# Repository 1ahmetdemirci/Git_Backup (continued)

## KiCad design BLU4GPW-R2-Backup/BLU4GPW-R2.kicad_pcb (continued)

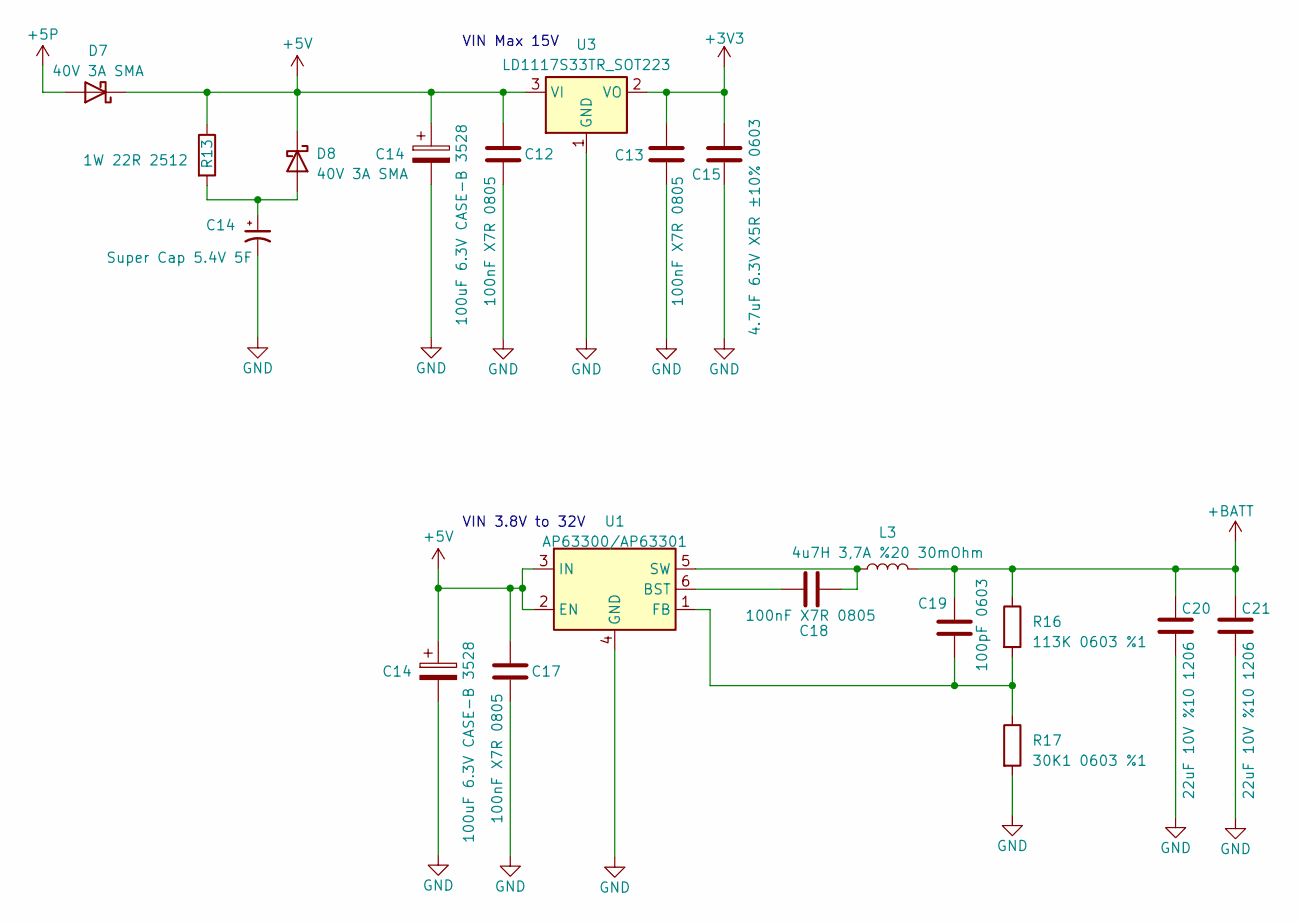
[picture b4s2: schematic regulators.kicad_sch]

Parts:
C12, C13, C17, C18: 100nF X7R 0805; C_0805_2012Metric
C14: Super Cap 5.4V 5F; DRML5R4505
C15: 4.7uF 6.3V X5R ±10% 0603; C_0603_1608Metric
C19: 100pF 0603; C_0603_1608Metric
C20, C21: 22uF 10V %10 1206; C_1206_3216Metric
D7, D8: 40V 3A SMA; D_SMA
L3: 4u7H 3,7A %20 30mOhm; SDR0805-1R5ML
R13: 1W 22R 2512; R_2512_6332Metric
R16: 113K 0603 %1; R_0603_1608Metric
R17: 30K1 0603 %1; R_0603_1608Metric
U1: AP63300/AP63301; AP63300
U3: LD1117S33TR_SOT223; SOT-223-3_TabPin2

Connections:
+5P: D7.2 (A); also elsewhere on the board
+BATT: C19.1, C20.1, C21.1, L3.2, R16.1; also elsewhere on the board
GND: C12.2, C13.2, C14.2, C15.2, C17.2, C20.2, C21.2, R17.2, U1.4 (GND), U3.1 (GND); also elsewhere on the board
unnamed: C18.2, U1.6 (BST)
unnamed: C19.2, R16.2, R17.1, U1.1 (FB)
unnamed: C18.1, L3.1, U1.5 (SW)

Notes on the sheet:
VIN 3.8V to 32V
VIN Max 15V

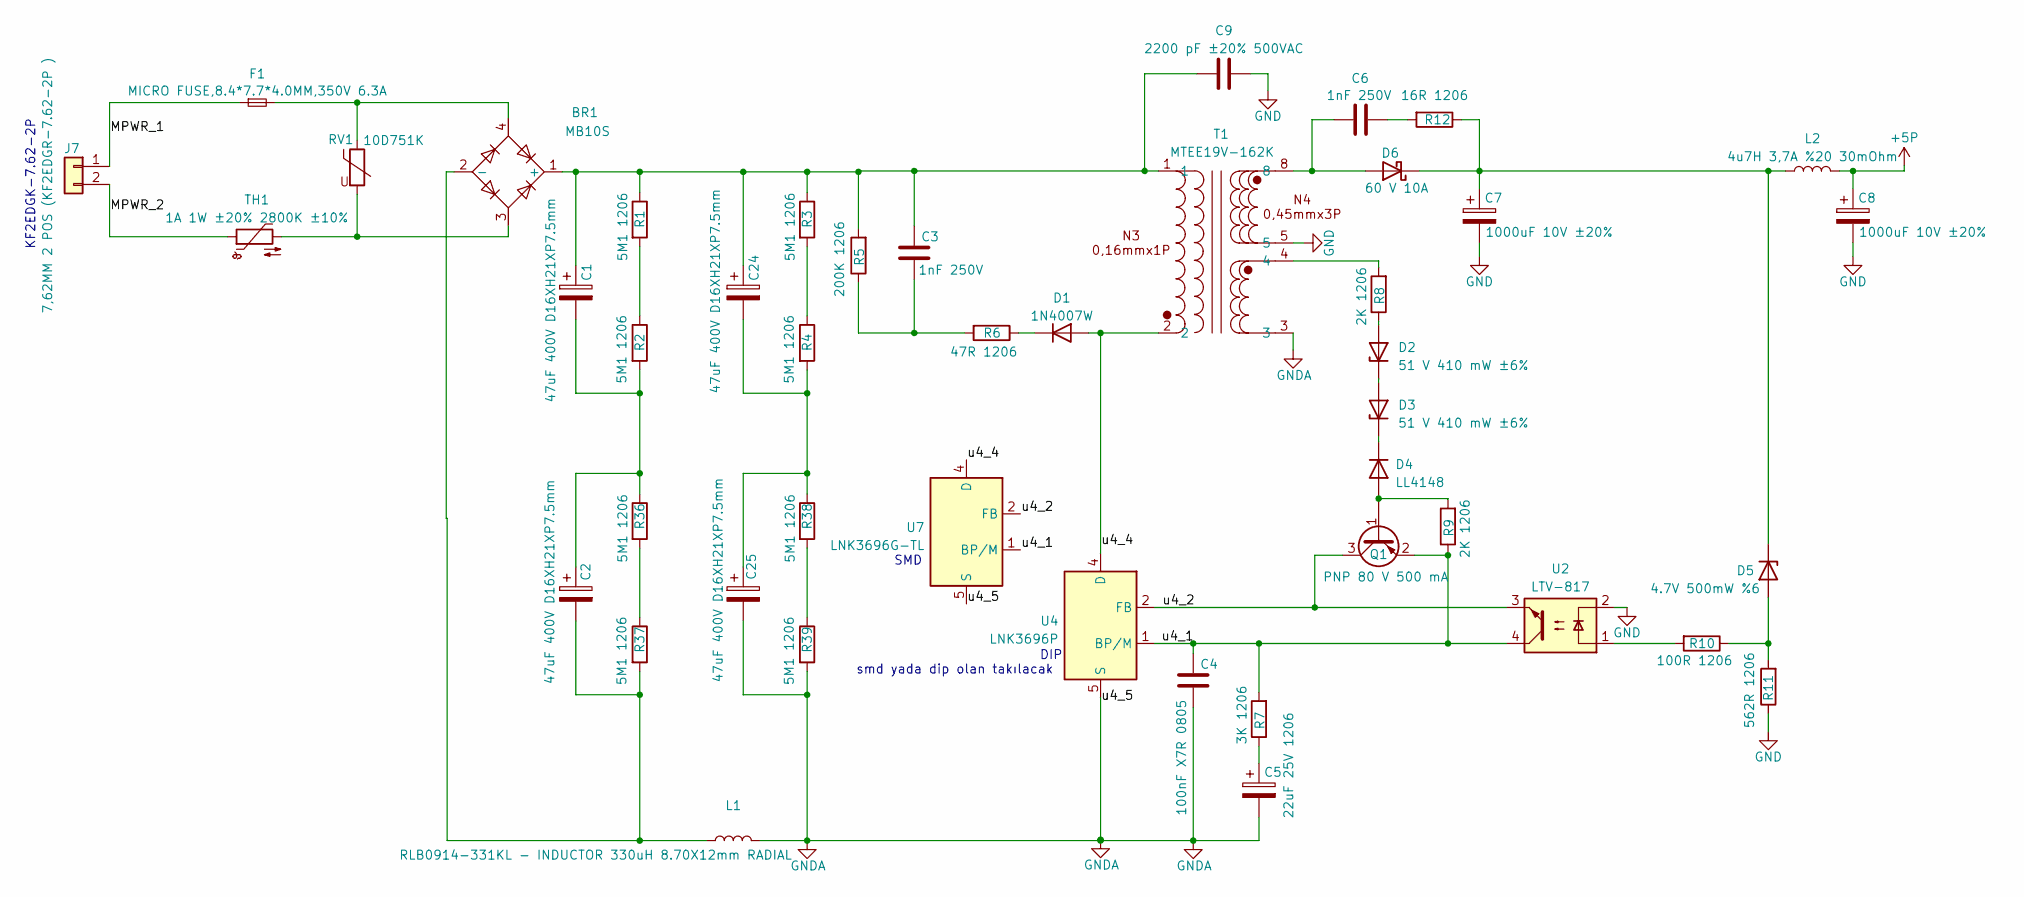
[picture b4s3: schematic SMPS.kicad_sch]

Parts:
BR1: MB10S
C1, C2, C24, C25: 47uF 400V D16XH21XP7.5mm; CP_Radial_D16H21P7.5mm
C3, C6: 1nF 250V; C_0805_2012Metric
C4: 100nF X7R 0805; C_0805_2012Metric
C5: 22uF 25V 1206; C_1206_3216Metric
C7, C8: 1000uF 10V ±20%; CP_Radial_D6.3mm_P2.50mm
C9: 2200 pF ±20% 500VAC; C_Disc_D8.0mm_W5.0mm_P10.00mm
D1: 1N4007W
D2, D3: 51 V 410 mW ±6%; BZT52C51-7-F
D4: LL4148; D_MiniMELF
D5: 4.7V 500mW %6; BZT52C51-7-F
D6: 60 V 10A; PPS1060
F1: MICRO FUSE,8.4*7.7*4.0MM,350V 6.3A; fuse_0697W
J7: 7,62MM 2 POS (KF2EDGR-7.62-2P ); PhoenixContact_GMSTBA_2,5_2-G-7,62_1x02_P7.62mm_Horizontal
L1: RLB0914-331KL - INDUCTOR 330uH 8.70X12mm RADIAL; L_Radial_D8.7mm_P5.00mm_Fastron_07HCP
L2: 4u7H 3,7A %20 30mOhm; SDR0805-1R5ML
Q1: PNP 80 V 500 mA; SOT-23
R1, R2, R3, R4, R36, R37, R38, R39: 5M1 1206; R_1206_3216Metric
R5: 200K 1206; R_1206_3216Metric
R6: 47R 1206; R_1206_3216Metric
R7: 3K 1206; R_1206_3216Metric
R8, R9: 2K 1206; R_1206_3216Metric
R10: 100R 1206; R_1206_3216Metric
R11: 562R 1206; R_1206_3216Metric
R12: 16R 1206; R_1206_3216Metric
RV1: 10D751K
T1: MTEE19V-162K
TH1: 1A 1W ±20% 2800K ±10%; MF72-10D7
U2: LTV-817; DIP-4_W7.62mm
U4: LNK3696P; PowerIntegrations_PDIP-8C
U7: LNK3696G-TL; PowerIntegrations_SMD-8C

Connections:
+5P: C8.1, L2.2; also elsewhere on the board
/SMPS/MPWR_1: F1.1, J7.1
/SMPS/MPWR_2: J7.2, TH1.1
/SMPS/u4_1: C4.1, Q1.2 (E), R7.2, R9.1, U2.4, U4.1 (BP/M), U7.1 (BP/M)
/SMPS/u4_2: Q1.3 (C), U2.3, U4.2 (FB), U7.2 (FB)
/SMPS/u4_4: D1.2 (A), T1.2, U4.4 (D), U7.4 (D)
GND: C7.2, C8.2, C9.2, R11.1, T1.5, U2.2; also elsewhere on the board
GNDA: C4.2, C5.2, C25.2, L1.2, R39.2, T1.3, U4.5 (S), U4.6 (S), U4.7 (S), U4.8 (S), U7.5 (S), U7.6 (S), U7.7 (S), U7.8 (S)
unnamed: BR1.1 (+), C1.1, C3.1, C9.1, C24.1, R1.1, R3.1, R5.2, T1.1
unnamed: BR1.2 (-), C2.2, L1.1, R37.2
unnamed: BR1.3, RV1.2, TH1.2
unnamed: BR1.4, F1.2, RV1.1
unnamed: C1.2, C2.1, R2.2, R36.1
unnamed: C3.2, R5.1, R6.2
unnamed: C5.1, R7.1
unnamed: C6.2, R12.2
unnamed: C24.2, C25.1, R4.2, R38.1
unnamed: D1.1 (K), R6.1
unnamed: D2.2 (A), R8.1
unnamed: D2.1 (K), D3.2 (A)
unnamed: D3.1 (K), D4.1 (K)
unnamed: D4.2 (A), Q1.1 (B), R9.2
unnamed: D5.2 (A), R10.1, R11.2
unnamed: C7.1, D5.1 (K), D6.1 (K), L2.1, R12.1
unnamed: C6.1, D6.2 (A), T1.8
unnamed: R1.2, R2.1
unnamed: R3.2, R4.1
unnamed: R8.2, T1.4
unnamed: R10.2, U2.1
unnamed: R36.2, R37.1
unnamed: R38.2, R39.1

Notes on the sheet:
SMD
smd yada dip olan takılacak
KF2EDGK-7.62-2P
DIP

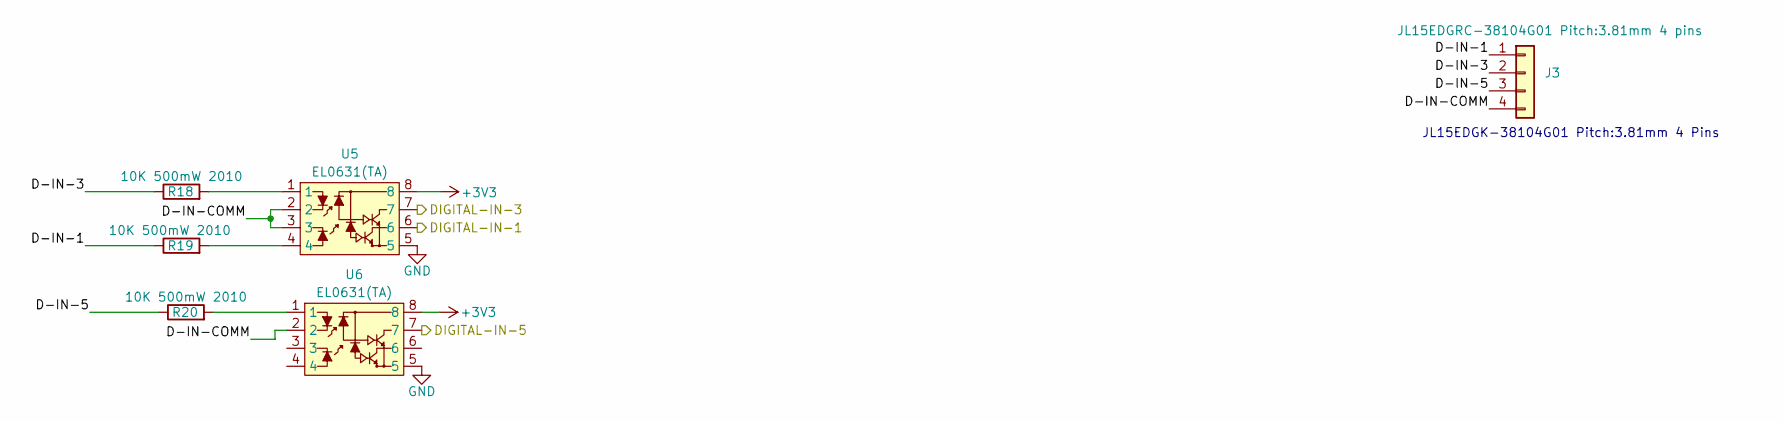
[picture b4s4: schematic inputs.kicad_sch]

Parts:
J3: JL15EDGRC-38104G01 Pitch:3.81mm 4 pins; 15EDGVC-3.81-04P-14-00SH
R18, R19, R20: 10K 500mW 2010; R_2010_5025Metric
U5, U6: EL0631(TA)

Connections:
/CONNECTION-COM/DIGITAL-IN-1: U5.6; also elsewhere on the board
/CONNECTION-COM/DIGITAL-IN-3: U5.7; also elsewhere on the board
/CONNECTION-COM/DIGITAL-IN-5: U6.7; also elsewhere on the board
/Inputs-outputs/D-IN-1: J3.1, R19.1
/Inputs-outputs/D-IN-3: J3.2, R18.1
/Inputs-outputs/D-IN-5: J3.3, R20.1
/Inputs-outputs/D-IN-COMM: J3.4, U5.2, U5.3, U6.2
GND: U5.5, U6.5; also elsewhere on the board
unnamed: R18.2, U5.1
unnamed: R19.2, U5.4
unnamed: R20.2, U6.1

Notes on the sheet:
JL15EDGK-38104G01 Pitch:3.81mm 4 Pins

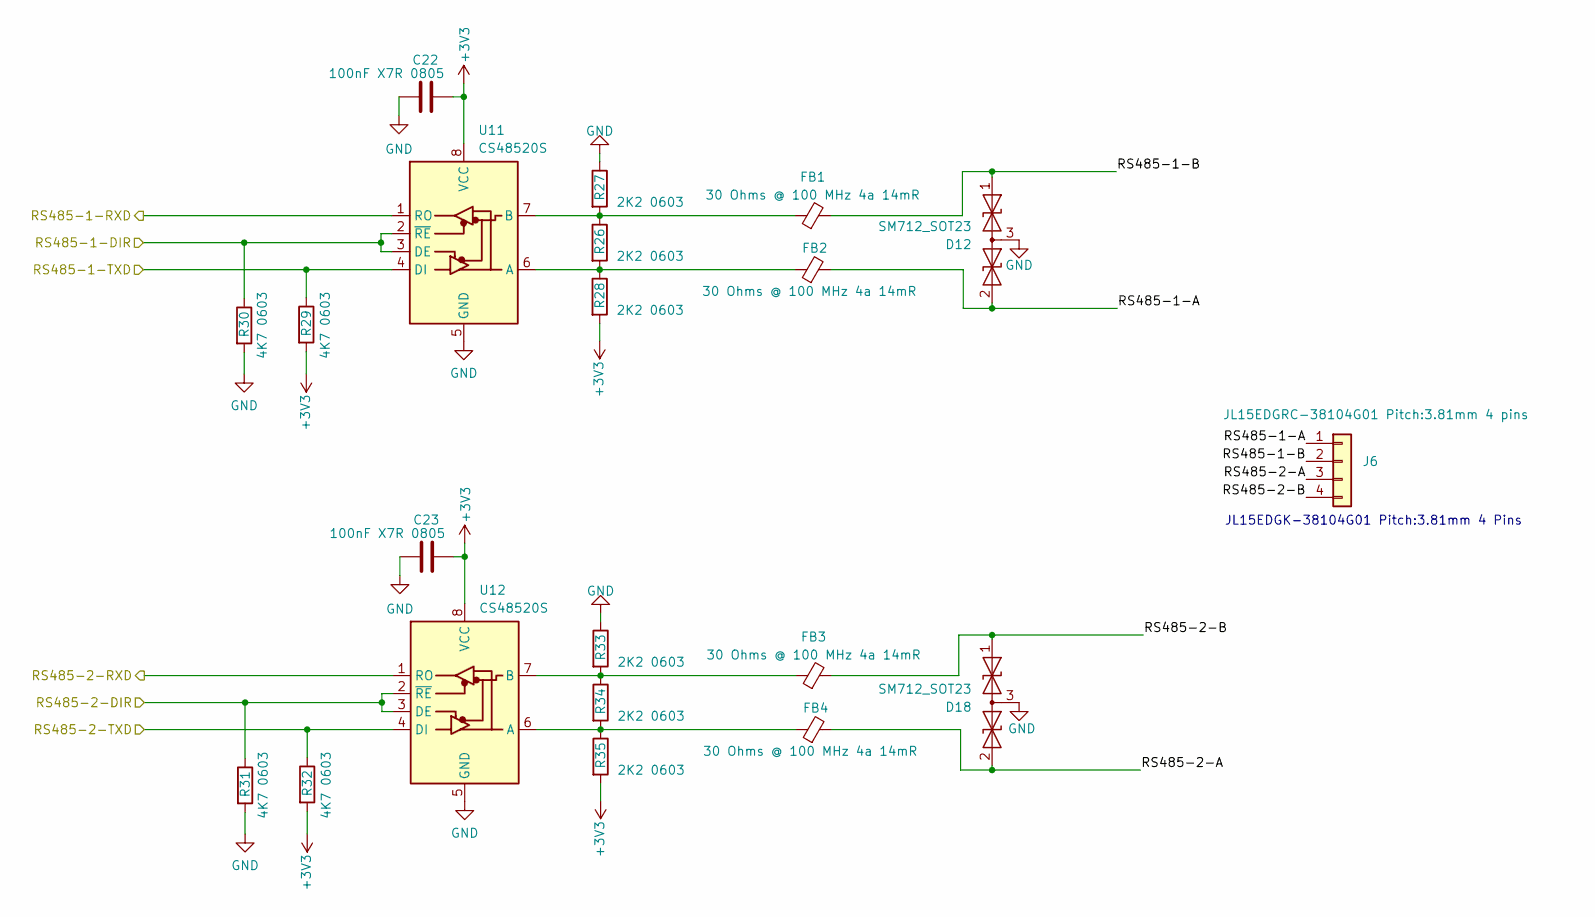
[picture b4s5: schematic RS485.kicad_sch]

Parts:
C22, C23: 100nF X7R 0805; C_0805_2012Metric
D12, D18: SM712_SOT23; SOT-23
FB1, FB2, FB3, FB4: 30 Ohms @ 100 MHz 4a 14mR; L_0805_2012Metric
J6: JL15EDGRC-38104G01 Pitch:3.81mm 4 pins; 15EDGVC-3.81-04P-14-00SH
R26, R27, R28, R33, R34, R35: 2K2 0603; R_0603_1608Metric
R29, R30, R31, R32: 4K7 0603; R_0603_1608Metric
U11, U12: CS48520S; PowerIntegrations_SO-8

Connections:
/CONNECTION-COM/RS485-1-DIR: R30.1, U11.2 (~RE), U11.3 (DE); also elsewhere on the board
/CONNECTION-COM/RS485-1-RXD: U11.1 (RO); also elsewhere on the board
/CONNECTION-COM/RS485-1-TXD: R29.1, U11.4 (DI); also elsewhere on the board
/CONNECTION-COM/RS485-2-DIR: R31.1, U12.2 (~RE), U12.3 (DE); also elsewhere on the board
/CONNECTION-COM/RS485-2-RXD: U12.1 (RO); also elsewhere on the board
/CONNECTION-COM/RS485-2-TXD: R32.1, U12.4 (DI); also elsewhere on the board
/RS485/RS485-1-A: D12.2 (A2), FB2.2, J6.1
/RS485/RS485-1-B: D12.1 (A1), FB1.2, J6.2
/RS485/RS485-2-A: D18.2 (A2), FB4.2, J6.3
/RS485/RS485-2-B: D18.1 (A1), FB3.2, J6.4
GND: C22.2, C23.2, D12.3 (common), D18.3 (common), R27.1, R30.2, R31.2, R33.1, U11.5 (GND), U12.5 (GND); also elsewhere on the board
unnamed: FB2.1, R26.2, R28.1, U11.6 (A)
unnamed: FB1.1, R26.1, R27.2, U11.7 (B)
unnamed: FB4.1, R34.2, R35.1, U12.6 (A)
unnamed: FB3.1, R33.2, R34.1, U12.7 (B)

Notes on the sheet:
JL15EDGK-38104G01 Pitch:3.81mm 4 Pins

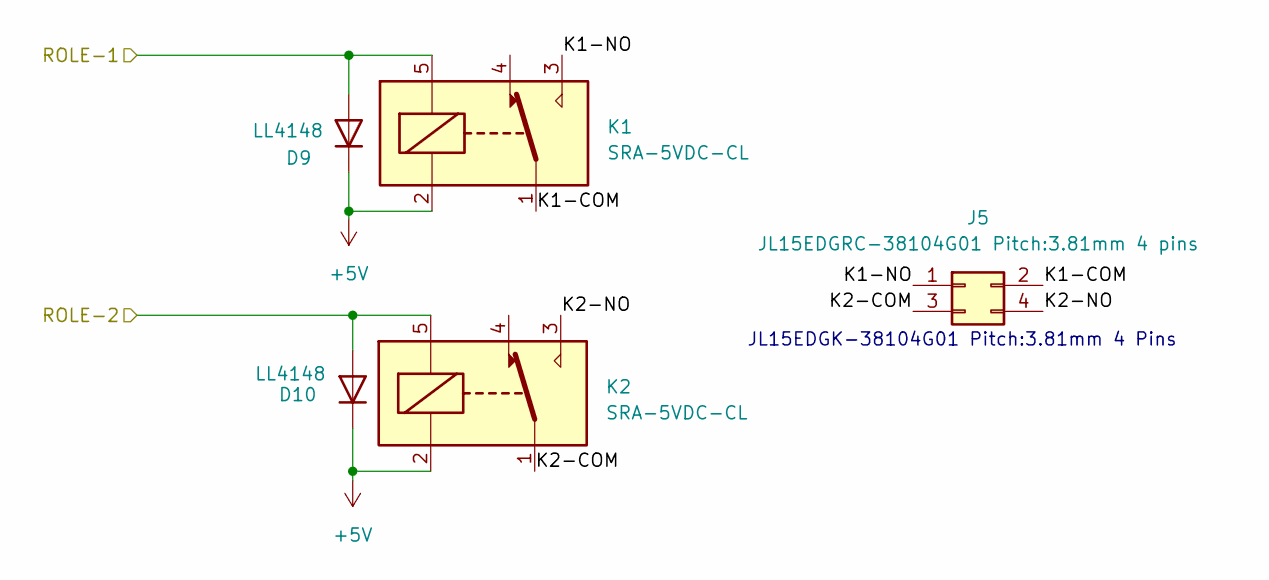
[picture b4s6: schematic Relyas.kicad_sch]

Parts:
D9, D10: LL4148; D_MiniMELF
J5: JL15EDGRC-38104G01 Pitch:3.81mm 4 pins; 15EDGVC-3.81-04P-14-00SH
K1, K2: SRA-5VDC-CL

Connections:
/CONNECTION-COM/ROLE-1: D9.2 (A), K1.5; also elsewhere on the board
/CONNECTION-COM/ROLE-2: D10.2 (A), K2.5; also elsewhere on the board
/Relays/K1-COM: J5.2, K1.1
/Relays/K1-NO: J5.1, K1.3
/Relays/K2-COM: J5.3, K2.1
/Relays/K2-NO: J5.4, K2.3

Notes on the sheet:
JL15EDGK-38104G01 Pitch:3.81mm 4 Pins

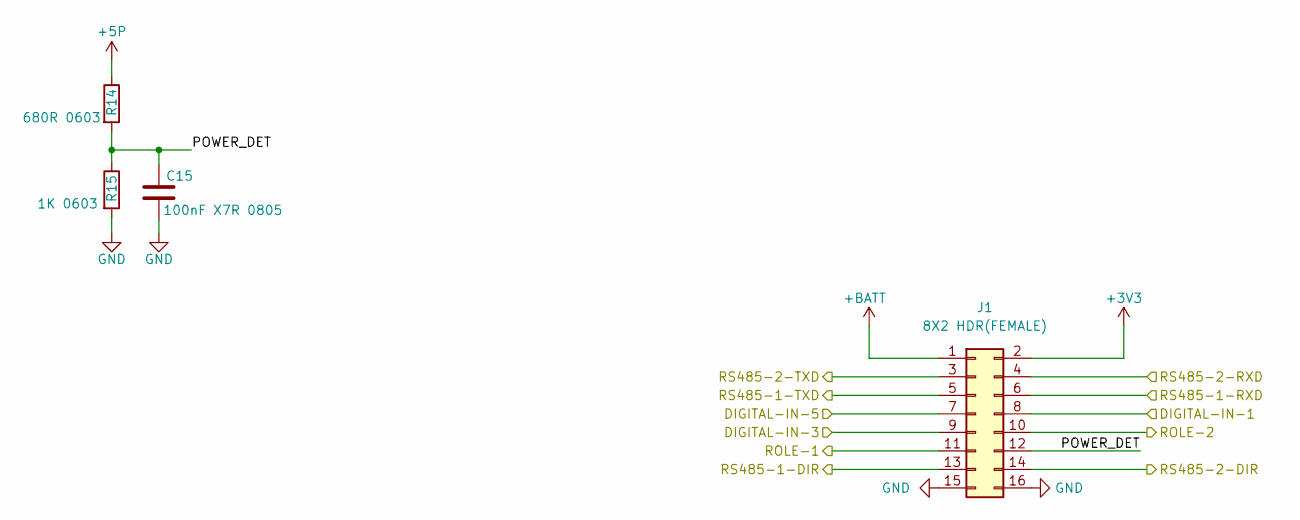
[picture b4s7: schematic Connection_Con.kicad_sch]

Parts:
C15: 100nF X7R 0805; C_0805_2012Metric
J1: 8X2 HDR(FEMALE); PinHeader_2x08_P2.54mm_Vertical
R14: 680R 0603; R_0603_1608Metric
R15: 1K 0603; R_0603_1608Metric

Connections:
+5P: R14.1; also elsewhere on the board
+BATT: J1.1; also elsewhere on the board
/CONNECTION-COM/DIGITAL-IN-1: J1.8; also elsewhere on the board
/CONNECTION-COM/DIGITAL-IN-3: J1.9; also elsewhere on the board
/CONNECTION-COM/DIGITAL-IN-5: J1.7; also elsewhere on the board
/CONNECTION-COM/ROLE-1: J1.11; also elsewhere on the board
/CONNECTION-COM/ROLE-2: J1.10; also elsewhere on the board
/CONNECTION-COM/RS485-1-DIR: J1.13; also elsewhere on the board
/CONNECTION-COM/RS485-1-RXD: J1.6; also elsewhere on the board
/CONNECTION-COM/RS485-1-TXD: J1.5; also elsewhere on the board
/CONNECTION-COM/RS485-2-DIR: J1.14; also elsewhere on the board
/CONNECTION-COM/RS485-2-RXD: J1.4; also elsewhere on the board
/CONNECTION-COM/RS485-2-TXD: J1.3; also elsewhere on the board
GND: C15.2, J1.15, J1.16, R15.2; also elsewhere on the board

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
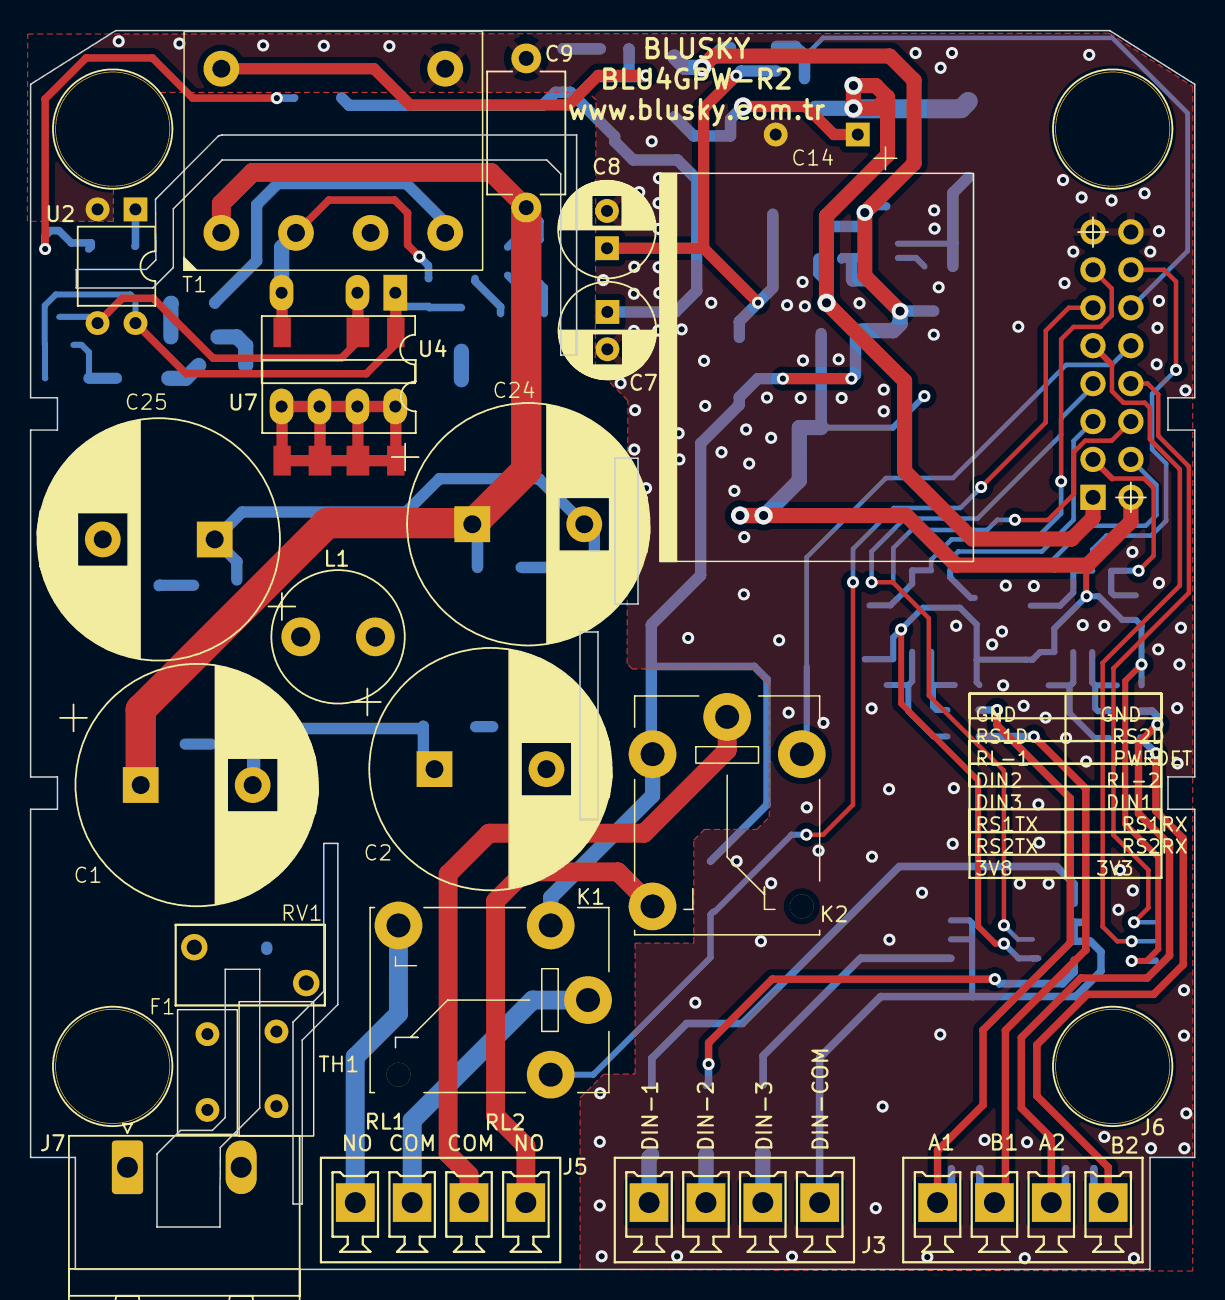
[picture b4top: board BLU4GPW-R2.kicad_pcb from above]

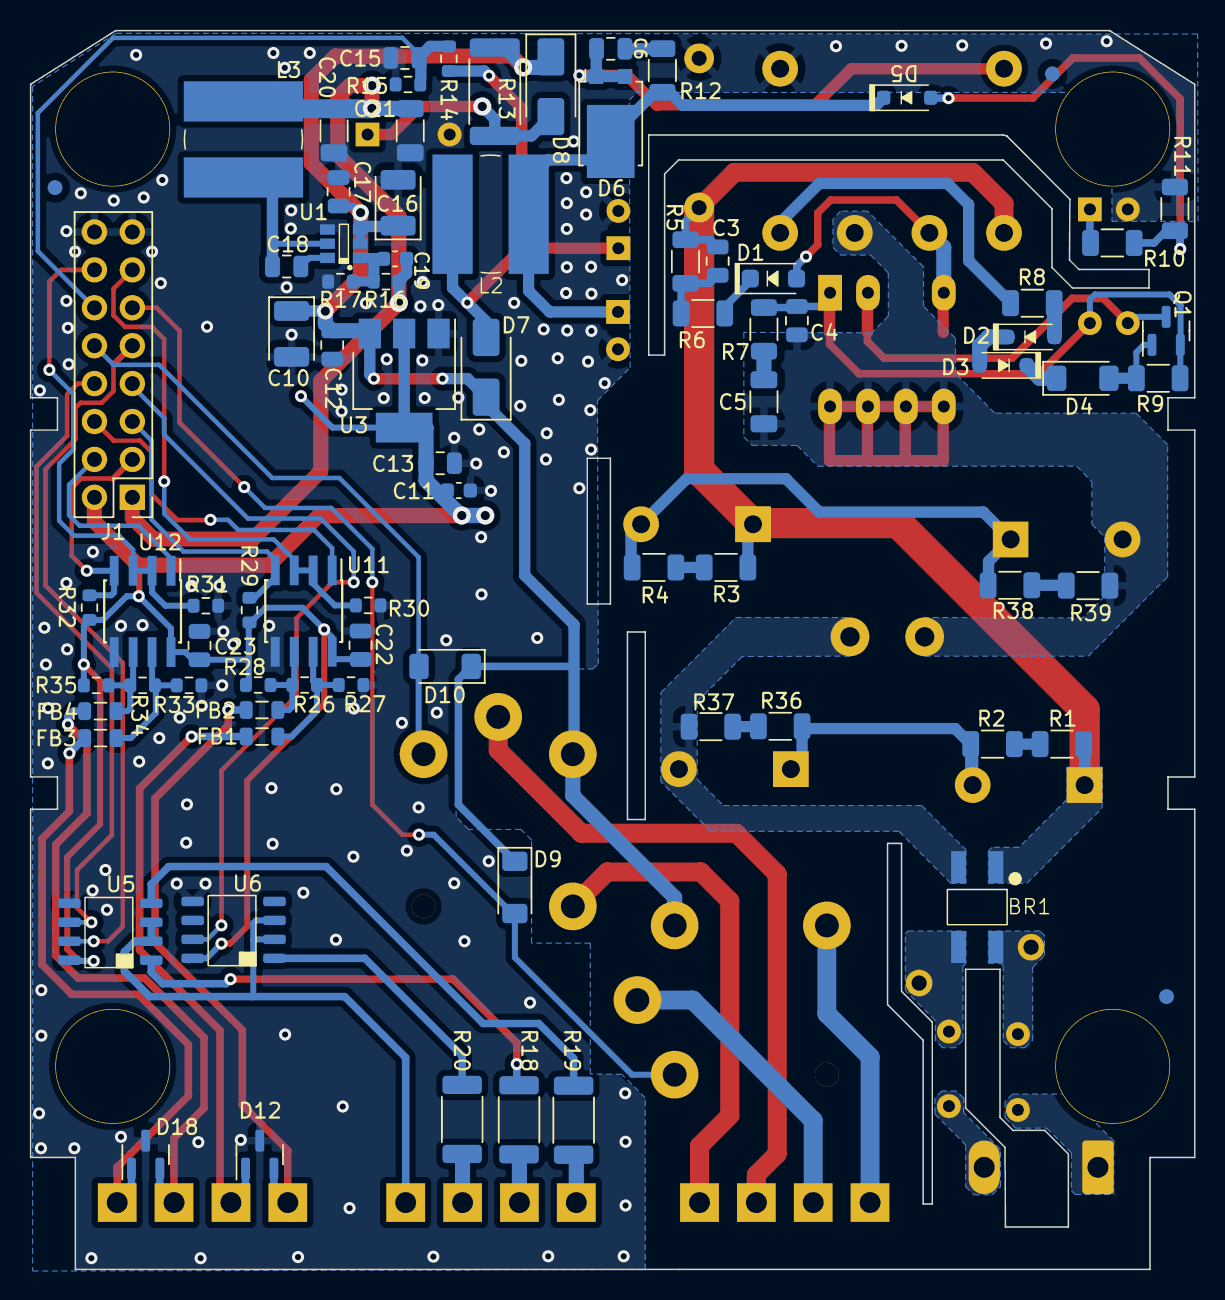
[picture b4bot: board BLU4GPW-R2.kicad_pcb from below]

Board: 2 copper layers, 78.0 x 83.0 mm, 104 parts (81 on the bottom side), 69 nets.

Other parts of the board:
C10, C16: 100uF 6.3V CASE-B 3528; CP_EIA-3528-12_Kemet-T
C11: 4.7uF 6.3V X5R ±10% 0603; C_0603_1608Metric
FID2, FID3: Fiducial; Fiducial_1mm_Mask2mm

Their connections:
GND: C10.2, C11.2, C16.2; also elsewhere on the board

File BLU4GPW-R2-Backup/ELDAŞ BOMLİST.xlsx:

Ref | QNTY (ADET) | Value (DEĞER) | Cmp name (PART ADI) | Footprint (İZDÜŞÜMÜ) | Description (AÇIKLAMA)
B1 | 1 | BLU4GP_Board | BLU4GP_Board | Aktif:BLULC-Power
BR1 | 1 | MB10S | MB10S | Aktif:MB10S
C1, C2, C24, C25 | 4 | 47uF 400V D16XH21XP7.5mm | C_Polarized | Aktif:CP_Radial_D16H21P7.5mm | Polarized capacitor
C3, C6 | 2 | 1nF 250V | C | Capacitor_SMD:C_0805_2012Metric | Unpolarized capacitor
C4, C12, C13, C15, C17, C18, C22, C23 | 8 | 100nF X7R 0805 | C | Capacitor_SMD:C_0805_2012Metric | Unpolarized capacitor
C5 | 1 | 22uF 25V 1206 | C_Polarized | Capacitor_SMD:C_1206_3216Metric | Polarized capacitor
C7, C8 | 2 | 1000uF 10V Â±20% | C_Polarized | Capacitor_THT:CP_Radial_D6.3mm_P2.50mm | Polarized capacitor
C9 | 1 | 2200 pF Â±20% 500VAC | C | Capacitor_THT:C_Disc_D8.0mm_W5.0mm_P10.00mm | Unpolarized capacitor
C10, C16 | 2 | 100uF 6.3V CASE-B 3528 | C_Polarized | Capacitor_Tantalum_SMD:CP_EIA-3528-12_Kemet-T | Polarized capacitor
C11 | 1 | 4.7uF 6.3V X5R Â±10% 0603 | C | Capacitor_SMD:C_0603_1608Metric | Unpolarized capacitor
C14 | 1 | Super Cap 5.4V 5F | C_Polarized_Small_US | Aktif:DRML5R4505 | Polarized capacitor, small US symbol
C19 | 1 | 100pF 0603 | C | Capacitor_SMD:C_0603_1608Metric | Unpolarized capacitor
C20, C21 | 2 | 22uF 10V %10 1206 | C | Capacitor_SMD:C_1206_3216Metric | Unpolarized capacitor
D1 | 1 | 1N4007W | D | Aktif:1N4007W | Diode
D2, D3 | 2 | 51 V 410 mW Â±6% | BZT52Bxx | Aktif:BZT52C51-7-F | 500mW Zener Diode, SOD-123F
D4, D9, D10 | 3 | LL4148 | LL4148 | Diode_SMD:D_MiniMELF | 100V 0.15A
D5 | 1 | 4.7V 500mW %6 | BZT52Bxx | Aktif:BZT52C51-7-F | 500mW Zener Diode, SOD-123F
D6 | 1 | 60 V 10A | D_Schottky | Aktif:PPS1060 | Schottky diode
D7, D8 | 2 | 40V 3A SMA | D_Schottky | Diode_SMD:D_SMA | Schottky diode
D12, D18 | 2 | SM712_SOT23 | SM712_SOT23 | Package_TO_SOT_SMD:SOT-23 | 7V/12V, 600W
F1 | 1 | MICRO FUSE,8.4*7.7*4.0MM,350V 6.3A | Fuse_Small | Aktif:fuse_0697W | Fuse, small symbol
FB1, FB2, FB3, FB4 | 4 | 30 Ohms @ 100 MHz 4a 14mR | FerriteBead_Small | Inductor_SMD:L_0805_2012Metric | Ferrite bead, small symbol
FID1, FID2, FID3 | 3 | Fiducial | Fiducial | Fiducial:Fiducial_1mm_Mask2mm | Fiducial Marker
J1 | 1 | 8X2 HDR(FEMALE) | Conn_02x08_Odd_Even | Connector_PinHeader_2.54mm:PinHeader_2x08_P2.54mm_Vertical | Generic connector, double row, 02x08
J3, J5, J6 | 3 | JL15EDGRC-38104G01 Pitch:3.81mm 4 pins | Conn_01x04 | enguru_28082018:15EDGVC-3.81-04P-14-00SH | Generic connector, single row, 01x04
J7 | 1 | 7,62MM 2 POS (KF2EDGR-7.62-2P ) | Conn_01x02 | Connector_Phoenix_GMSTB:PhoenixContact_GMSTBA_2,5_2-G-7,62_1x02_P7.62mm_Horizon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 | Generic connector, single row, 01x02
K1, K2 | 2 | SRA-5VDC-CL | G5LE-1 | Aktif:SRA-5VDC-CL | Omron G5LE relay
L1 | 1 | RLB0914-331KL - INDUCTOR 330uH 8.70X12mm RADIAL | L | Inductor_THT:L_Radial_D8.7mm_P5.00mm_Fastron_07HCP | Inductor
L2, L3 | 2 | 4u7H 3,7A %20 30mOhm | L | Aktif:SDR0805-1R5ML | Inductor
Q1 | 1 | PNP 80 V 500 mA | Q_PNP_BEC | Package_TO_SOT_SMD:SOT-23 | PNP transistor, base/emitter/collector
R1, R2, R3, R4, R36, R37, R38, R39 | 8 | 5M1 1206 | R | Resistor_SMD:R_1206_3216Metric | Resistor
R5 | 1 | 200K 1206 | R | Resistor_SMD:R_1206_3216Metric | Resistor
R6 | 1 | 47R 1206 | R | Resistor_SMD:R_1206_3216Metric | Resistor
R7 | 1 | 3K 1206 | R | Resistor_SMD:R_1206_3216Metric | Resistor
R8, R9 | 2 | 2K 1206 | R | Resistor_SMD:R_1206_3216Metric | Resistor
R10 | 1 | 100R 1206 | R | Resistor_SMD:R_1206_3216Metric | Resistor
R11 | 1 | 562R 1206 | R | Resistor_SMD:R_1206_3216Metric | Resistor
R12 | 1 | 16R 1206 | R | Resistor_SMD:R_1206_3216Metric | Resistor
R13 | 1 | 1W 22R 2512 | R | Resistor_SMD:R_2512_6332Metric | Resistor
R14 | 1 | 680R 0603 | R | Resistor_SMD:R_0603_1608Metric | Resistor
R15 | 1 | 1K 0603 | R | Resistor_SMD:R_0603_1608Metric | Resistor
R16 | 1 | 113K 0603 %1 | R | Resistor_SMD:R_0603_1608Metric | Resistor
R17 | 1 | 30K1 0603 %1 | R | Resistor_SMD:R_0603_1608Metric | Resistor
R18, R19, R20 | 3 | 10K 500mW 2010 | R | Resistor_SMD:R_2010_5025Metric | Resistor
R26, R27, R28, R33, R34, R35 | 6 | 2K2 0603 | R | Resistor_SMD:R_0603_1608Metric | Resistor
R29, R30, R31, R32 | 4 | 4K7 0603 | R | Resistor_SMD:R_0603_1608Metric | Resistor
RV1 | 1 | 10D751K | Varistor | Aktif:10D751K | Voltage dependent resistor
T1 | 1 | MTEE19V-162K | MTEE19V-162K | Aktif:MTEE19V-162K
TH1 | 1 | 1A 1W Â±20% 2800K Â±10% | Thermistor_NTC | Aktif:MF72-10D7 | Temperature dependent resistor
U1 | 1 | AP63300/AP63301 | AP63200WU | Aktif:AP63300 | 2A, 500kHz Buck DC/DC Converter
U2 | 1 | LTV-817 | LTV-817 | Package_DIP:DIP-4_W7.62mm | DC Optocoupler
U3 | 1 | LD1117S33TR_SOT223 | LD1117S33TR_SOT223 | Package_TO_SOT_SMD:SOT-223-3_TabPin2 | 800mA Fixed Low Drop Positive
U4 | 1 | LNK3696P | LNK3206D | Package_DIP:PowerIntegrations_PDIP-8C | LinkSwitch-TN2 Family
U5, U6 | 2 | EL0631(TA) | EL0631(TA) | Aktif:EL0631(TA)
U7 | 1 | LNK3696G-TL | LNK3206D | Package_DIP:PowerIntegrations_SMD-8C | LinkSwitch-TN2 Family
U11, U12 | 2 | CS48520S | MAX485E | Package_SO:PowerIntegrations_SO-8 | Half duplex RS-485/RS-422
